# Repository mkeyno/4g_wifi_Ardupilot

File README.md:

# ArduPilot Project
This project intends to port [ArduPilot](https://github.com/ArduPilot/ardupilot) firmware on new hardware base on embedded Linux multiple-core system and ESP32.
The main purpose of this project is to extend Modular design & hardware abstract layer base on processing and task.
- ESP32 is double core processor with mature RTOS firmware. One core dedicated for IMU data fusing and main autopilot function (Stabilize, Attitude control, Navigation) other core responsible for communication, auxiliary module management and ground station. its 2.4 Ghz wifi link is sitable for local data link between drone and ground station 
- separate IO module, manage pilot commands and drone actuators data for main core system and it only exchange data on bus line in standard communication protocol (I2C, SPI, Serial), this reduce processor resources and complexity of main code, because each part is responsible for processing its own data (hardware encapsulation).IO module can be made with any designed hardware and software base on drone specification and just need to put data on TX buffer and received command from RX buffer. In this project I use same IC in Ardupilot hardware (STM32f103C8T6). Primary hardware design located at [here](Hardware/IO_Modules/readme.md) 
- Multiple-core embedded Linux system is auxiliary  core system  which can provide secondary & backup IMU data, GPS data, advance terrain navigation , 4G video streaming and any hardware management for enhancing drone capabilities. Similar to IO module this also has its own development platform base on popular Linux  
following is the block diagram and functional modules chart for this project

## Project Motivation ##
This idea came to mind when I intent to add camera on Ardupilot hardware and establish the video link under 4G network. 
SimCom 7100 & 7600 were first choice as I was familiar with Arduino GPRS shield made of SimCom product and are cheap , 
however after digging around those product I’ve noticed  the only available firmware (AT Command) is not mature enough to add camera and work as slave supplementary hardware for Ardupilot master board .
Unfortunately [SimCom]() has not provided yet any open SDK for IoT developer , hence I look to the other 4G modules in market such as [Telit]( https://www.telit.com)  , [InnoCom]( https://www.innocomm.com), [Gemalto]( https://www.gemalto.com), [Multitech]( https://www.multitech.com/), [Sierra Wireless]( https://www.sierrawireless.com), [Quectel]( https://www.quectel.com)
I found [Airprime WPx5xx-76xx series](https://source.sierrawireless.com/devices/wp-series/wp7502/) very Promising and elegant. 
while Airprime series has powerful and rich hardware with multi core, it also  embedded with Linux and open source SDK  for IoT developer 
summary of this product specification  come as follow
The AirPrime WP75xx/AirPrime WP8548 is a powerful multiple-core system that includes:
- One QDSP6 core, embedding Telecom firmware with integrated cellular voice (future firmware release), data and wireless Internet connectivity
- One Cortex-A5 core entirely dedicated to customer application and natively provided with Linux operating system
The application processor memory is dedicated to the Legato platform, including:
    - Linux kernel
    - Root file system
    - Application framework
    - Customer applications

- Memory Details WP75xx / WP8548
Flash Total 512 MB
    -256 MB Reserved for Application processor 
- RAM Total 256 MB
    -128 MB Reserved for Application processor 

## Milestone ##
- Hardware Design:
  - ***4G board***: base on Airprime
  - ***ESP32 board***:   
  - ***Input board***:   
  - ***Output board***:   
- Hardware prototype:  
- Firmware porting: 
- Test & debug: 

## License ##

This project is licensed under the GNU General Public License, version 3.

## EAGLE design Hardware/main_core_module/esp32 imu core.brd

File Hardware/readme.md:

This is repository for all hardware design and resources

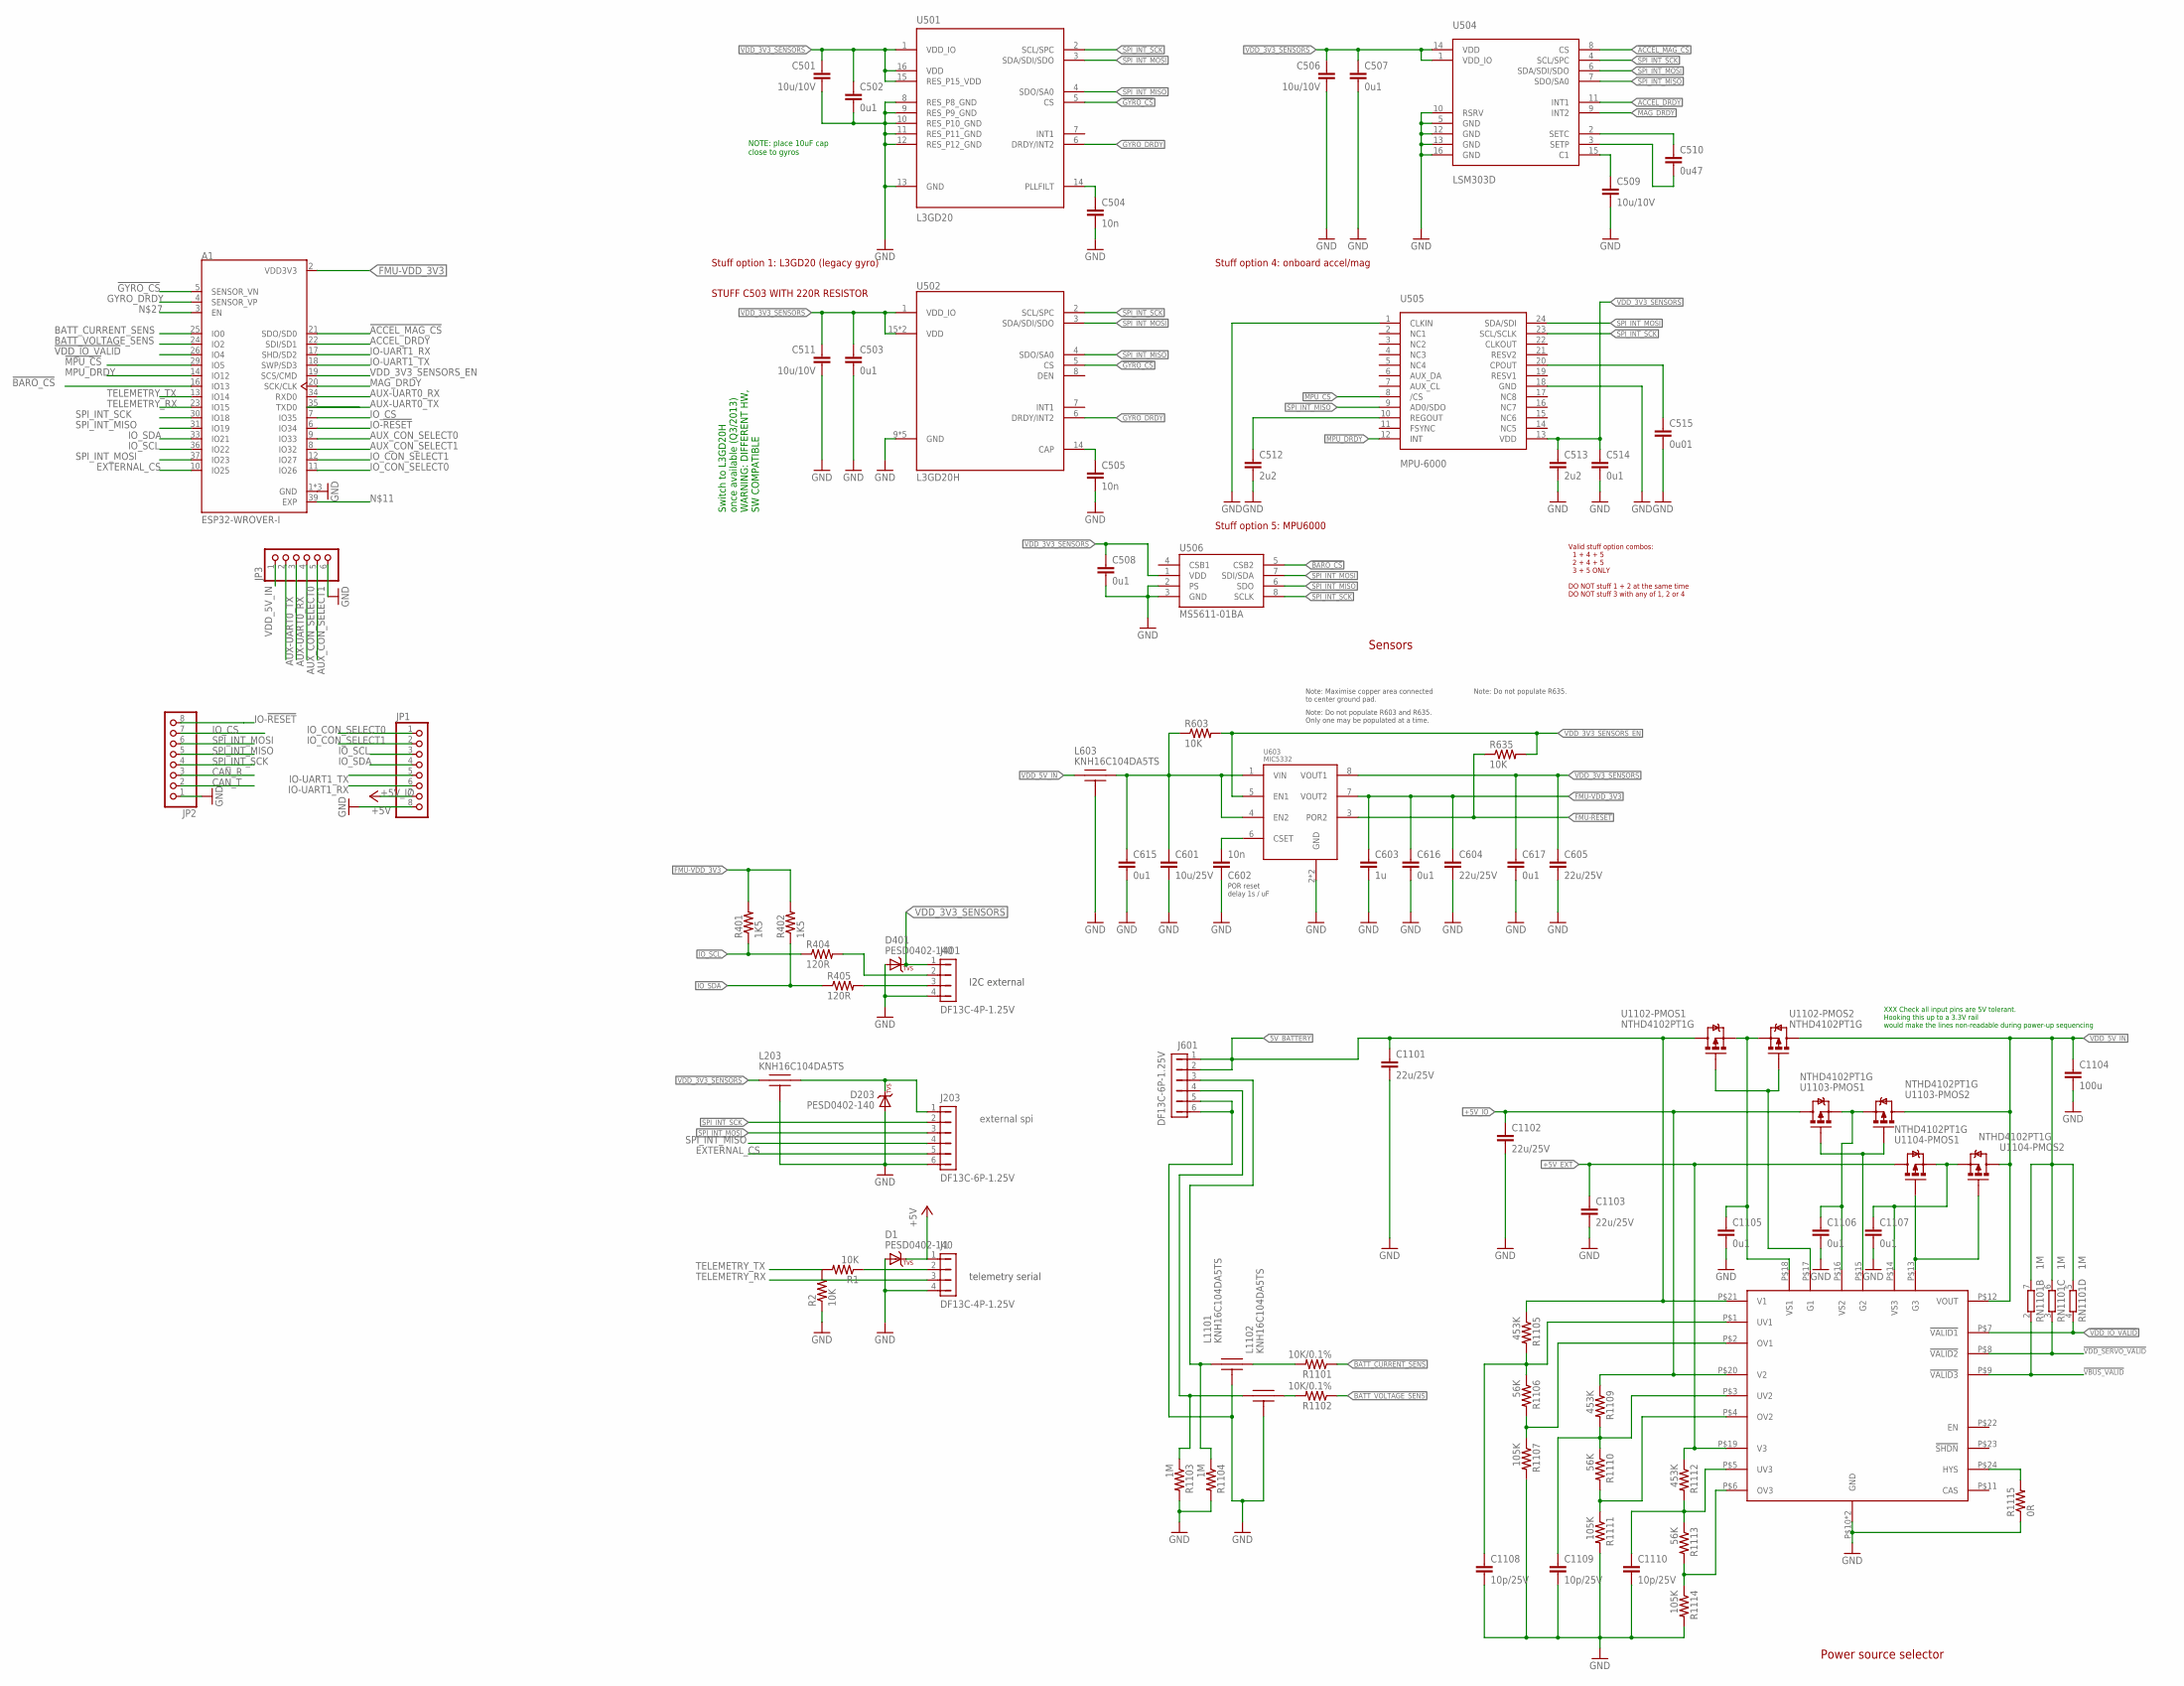
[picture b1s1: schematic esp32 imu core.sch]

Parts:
A1: ESP32-WROVER-I; XCVR_ESP32-WROVER-I
C501, C506, C509, C511: 10u/10V; 0805-CAP; PARTNO CC0805ZKY5V6BB106
C502, C503, C507, C508, C514, C615, C616, C617: 0u1; 0402-CAP; PARTNO CC0402ZRY5V7BB104
C504, C505, C602: 10n; 0402-CAP; PARTNO CC0402KRX7R7BB103
C510: 0u47; 0402-CAP; PARTNO C1005X5R1C474K050BC
C512, C513: 2u2; 0603-CAP; PARTNO C1608X6S1C225K080AC
C515: 0u01; 0603-CAP; PARTNO 06033C103JAT2A
C601: 10u/25V; 0805-CAP; PARTNO CL21A106KAYNNNE
C603: 1u; 0603-CAP; PARTNO CC0603ZRY5V7BB105
C604, C605, C1101, C1102, C1103: 22u/25V; 0805-CAP; PARTNO CL21A226MAQNNNE
C1104: 100u; 1206-CAP; PARTNO C3216X5R1A107M160AC
C1105, C1106, C1107: 0u1; 0402-CAP; PARTNO C1005X7R1E104K050BB
C1108, C1109, C1110: 10p/25V; 0402-CAP; PARTNO C0402C100J3GACTU
D1, D203, D401: PESD0402-140; 0402-TVS; PARTNO PESD0402-140
J1, J401: DF13C-4P-1.25V; PARTNO DF13C-4P-1.25V(20)
J203, J601: DF13C-6P-1.25V; PARTNO DF13C-6P-1.25V(20)
JP1, JP2: PINHD-1X8; 1X08
JP3: PINHD-1X6; 1X06
L203, L603, L1101, L1102: KNH16C104DA5TS; KYOCERA-KNH16-DA; PARTNO KNH16C104DA5TS
R1, R2, R603, R635: 10K; 0402-RES; PARTNO RC0402FR-0710KL
R401, R402: 1K5; 0402-RES; PARTNO RC0402FR-071K5L
R404, R405: 120R; 0402-RES; PARTNO RC0402FR-07120RL
R1101, R1102: 10K/0.1%; 0402-RES; PARTNO ERA-2AEB103X
R1103, R1104: 1M; 0402-RES; PARTNO RC0402FR-071ML
R1105, R1109, R1112: 453K; 0402-RES; PARTNO RMCF0402FT453K
R1106, R1110, R1113: 56K; 0402-RES; PARTNO ERA-2AEB563X
R1107, R1111, R1114: 105K; 0402-RES; PARTNO ERJ-2RKF1053X
R1115: 0R; 0402-RES; PARTNO ERJ-2GE0R00X
RN1101: 1M; EXB28V; PARTNO EXB-28V105JX
U501: L3GD20; L3G4200DH-MAN; PARTNO L3GD20
U502: L3GD20H; LGA-16L; PARTNO L3GD20H
U504: LSM303D; LGA-16L; PARTNO LSM303D
U505: MPU-6000; QFN-24; PARTNO MPU-6000
U506: MS5611-01BA; PARTNO MS5611-01BA
U603: MIC5332; MLF-8-EPAD; PARTNO MIC5332-SSYMT
U1101: LTC4417; MO-220; PARTNO LTC4417IUF#PBF
U1102, U1103, U1104: NTHD4102PT1G; 1206-8; PARTNO NTHD4102PT1G

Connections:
5V_BATTERY: C1101.P$1 (1), J601.1, J601.2, R1105.P$1 (1), U1101.P$21 (V1), U1102.P$7 (D), U1102.P$8 (D)
!ACCEL_MAG_CS: A1.21 (SDO/SD0), U504.8 (CS)
!BARO_CS: A1.16 (IO13), U506.5 (CSB2)
!GYRO_CS: A1.5 (SENSOR_VN), U501.5 (CS), U502.5 (CS)
!MPU_CS: A1.29 (IO5), U505.8 (/CS)
!VBUS_VALID: RN1101.2 (1), U1101.P$9 (!VALID3)
!VDD_IO_VALID: A1.26 (IO4), RN1101.4 (1), U1101.P$7 (!VALID1)
!VDD_SERVO_VALID: RN1101.3 (1), U1101.P$8 (!VALID2)
+5V_EXT: C1103.P$1 (1), D1.C, J1.1, R1112.P$1 (1), U1101.P$19 (V3), U1104.P$7 (D), U1104.P$8 (D)
+5V_IO: C1102.P$1 (1), JP1.7, R1109.P$1 (1), U1101.P$20 (V2), U1103.P$7 (D), U1103.P$8 (D)
ACCEL_DRDY: A1.22 (SDI/SD1), U504.11 (INT1)
AUX-UART0_RX: A1.34 (RXD0), JP3.3
AUX-UART0_TX: A1.35 (TXD0), JP3.2
AUX_CON_SELECT0: A1.9 (IO33), JP3.4
AUX_CON_SELECT1: A1.8 (IO32), JP3.5
BATT_CURRENT_SENS: A1.25 (IO0), R1101.P$1 (1)
BATT_CURRENT_SENS_PROT: J601.3, L1101.P$1, R1104.P$1 (1)
BATT_VOLTAGE_SENS: A1.24 (IO2), R1102.P$1 (1)
BATT_VOLTAGE_SENS_PROT: J601.4, L1102.P$1, R1103.P$1 (1)
CAN_R: JP2.3
CAN_T: JP2.2
EXTERNAL_CS: A1.10 (IO25), J203.5
FMU-!RESET: R635.P$1 (1), U603.3 (POR2)
FMU-VDD_3V3: A1.2 (VDD3V3), C603.P$1 (1), C604.P$1 (1), C616.P$1 (1), R401.P$2 (2), R402.P$2 (2), U603.7 (VOUT2)
FMU-VDD_5V5: C601.P$1 (1), C615.P$1 (1), L603.P$2, R603.P$1 (1), U603.1 (VIN), U603.4 (EN2)
GND: A1.1 (GND), A1.15 (GND), A1.38 (GND), C501.P$2 (2), C502.P$2 (2), C503.P$2 (2), C504.P$2 (2), C505.P$2 (2), C506.P$2 (2), C507.P$2 (2), C508.P$2 (2), C509.P$2 (2), C511.P$2 (2), C512.P$2 (2), C513.P$2 (2), C514.P$2 (2), C515.P$2 (2), C601.P$2 (2), C602.P$1 (1), C603.P$2 (2), C604.P$2 (2), C605.P$2 (2), C615.P$2 (2), C616.P$2 (2), C617.P$2 (2), C1101.P$2 (2), C1102.P$2 (2), C1103.P$2 (2), C1104.P$2 (2), C1105.P$2 (2), C1106.P$2 (2), C1107.P$2 (2), C1108.P$2 (2), C1109.P$2 (2), C1110.P$2 (2), D1.A, D203.A, D401.A, J1.4, J203.6, J401.4, J601.5, J601.6, JP1.8, JP2.1, JP3.6, L203.P$3, L203.P$4, L203.P$5, L603.P$3, L603.P$4, L603.P$5, L1101.P$3, L1101.P$4, L1101.P$5, L1102.P$3, L1102.P$4, L1102.P$5, R2.P$1 (1), R1103.P$2 (2), R1104.P$2 (2), R1107.P$2 (2), R1111.P$2 (2), R1114.P$2 (2), R1115.P$1 (1), U501.8 (RES_P8_GND), U501.9 (RES_P9_GND), U501.10 (RES_P10_GND), U501.11 (RES_P11_GND), U501.12 (RES_P12_GND), U501.13 (GND), U502.9 (GND), U502.10 (GND), U502.11 (GND), U502.12 (GND), U502.13 (GND), U504.5 (GND), U504.10 (RSRV), U504.12 (GND), U504.13 (GND), U504.16 (GND), U505.1 (CLKIN), U505.18 (GND), U506.2 (PS), U506.3 (GND), U603.2 (GND), U603.GND, U1101.P$10 (GND), U1101.P$25 (GND)
GYRO_DRDY: A1.4 (SENSOR_VP), U501.6 (DRDY/INT2), U502.6 (DRDY/INT2)
IO-!RESET: A1.6 (IO34), JP2.8
IO-UART1_RX: A1.17 (SHD/SD2), JP1.6
IO-UART1_TX: A1.18 (SWP/SD3), JP1.5
IO_CON_SELECT0: A1.11 (IO26), JP1.1
IO_CON_SELECT1: A1.12 (IO27), JP1.2
IO_CS: A1.7 (IO35), JP2.7
IO_SCL: A1.36 (IO22), JP1.3, R401.P$1 (1), R404.P$1 (1)
IO_SDA: A1.33 (IO21), JP1.4, R402.P$1 (1), R405.P$1 (1)
MAG_DRDY: A1.20 (SCK/CLK), U504.9 (INT2)
MPU_DRDY: A1.14 (IO12), U505.12 (INT)
unnamed: J1.2, R1.P$1 (1)
unnamed: C509.P$1 (1), U504.15 (C1)
unnamed: C510.P$1 (1), U504.2 (SETC)
unnamed: C510.P$2 (2), U504.3 (SETP)
unnamed: C505.P$1 (1), U502.14 (CAP)
unnamed: J401.2, R404.P$2 (2)
unnamed: C504.P$1 (1), U501.14 (PLLFILT)
unnamed: J401.3, R405.P$2 (2)
unnamed: C602.P$2 (2), U603.6 (CSET)
unnamed: C1108.P$1 (1), R1105.P$2 (2), R1106.P$1 (1), U1101.P$1 (UV1)
unnamed: C512.P$1 (1), U505.10 (REGOUT)
unnamed: C515.P$1 (1), U505.20 (CPOUT)
unnamed: R1106.P$2 (2), R1107.P$1 (1), U1101.P$2 (OV1)
unnamed: C1109.P$1 (1), R1109.P$2 (2), R1110.P$1 (1), U1101.P$3 (UV2)
unnamed: R1110.P$2 (2), R1111.P$1 (1), U1101.P$4 (OV2)
unnamed: R1113.P$2 (2), R1114.P$1 (1), U1101.P$6 (OV3)
unnamed: C1110.P$1 (1), R1112.P$2 (2), R1113.P$1 (1), U1101.P$5 (UV3)
unnamed: C1105.P$1 (1), U1101.P$18 (VS1), U1102.P$1 (S), U1102.P$3 (S)
unnamed: D203.C, J203.1, L203.P$2
unnamed: L1102.P$2, R1102.P$2 (2)
unnamed: L1101.P$2, R1101.P$2 (2)
unnamed: R1115.P$2 (2), U1101.P$24 (HYS)
unnamed: C1106.P$1 (1), U1101.P$16 (VS2), U1103.P$1 (S), U1103.P$3 (S)
unnamed: C1107.P$1 (1), U1101.P$14 (VS3), U1104.P$1 (S), U1104.P$3 (S)
unnamed: U1101.P$13 (G3), U1104.P$2 (G), U1104.P$4 (G)
unnamed: U1101.P$15 (G2), U1103.P$2 (G), U1103.P$4 (G)
unnamed: U1101.P$17 (G1), U1102.P$2 (G), U1102.P$4 (G)
SPI_INT_MISO: A1.31 (IO19), J203.4, JP2.5, U501.4 (SDO/SA0), U502.4 (SDO/SA0), U504.7 (SDO/SA0), U505.9 (AD0/SDO), U506.6 (SDO)
SPI_INT_MOSI: A1.37 (IO23), J203.3, JP2.6, U501.3 (SDA/SDI/SDO), U502.3 (SDA/SDI/SDO), U504.6 (SDA/SDI/SDO), U505.24 (SDA/SDI), U506.7 (SDI/SDA)
SPI_INT_SCK: A1.30 (IO18), J203.2, JP2.4, U501.2 (SCL/SPC), U502.2 (SCL/SPC), U504.4 (SCL/SPC), U505.23 (SCL/SCLK), U506.8 (SCLK)
TELEMETRY_RX: A1.23 (IO15), J1.3
TELEMETRY_TX: A1.13 (IO14), R1.P$2 (2), R2.P$2 (2)
VDD_3V3_SENSORS: C501.P$1 (1), C502.P$1 (1), C503.P$1 (1), C506.P$1 (1), C507.P$1 (1), C508.P$1 (1), C511.P$1 (1), C513.P$1 (1), C514.P$1 (1), C605.P$1 (1), C617.P$1 (1), D401.C, J401.1, L203.P$1, U501.1 (VDD_IO), U501.15 (RES_P15_VDD), U501.16 (VDD), U502.1 (VDD_IO), U502.15 (VDD), U502.16 (VDD), U504.1 (VDD_IO), U504.14 (VDD), U505.13 (VDD), U506.1 (VDD), U603.8 (VOUT1)
VDD_3V3_SENSORS_EN: A1.19 (SCS/CMD), R603.P$2 (2), R635.P$2 (2), U603.5 (EN1)
VDD_5V_IN: C1104.P$1 (1), JP3.1, L603.P$1, RN1101.5 (2), RN1101.6 (2), RN1101.7 (2), U1101.P$12 (VOUT), U1102.P$5 (D), U1102.P$6 (D), U1103.P$5 (D), U1103.P$6 (D), U1104.P$5 (D), U1104.P$6 (D)

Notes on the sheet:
Sensors
Switch to L3GD20H once available (Q3/2013) WARNING: DIFFERENT HW, SW COMPATIBLE
NOTE: place 10uF cap close to gyros
Stuff option 1: L3GD20 (legacy gyro)
Stuff option 4: onboard accel/mag
Valid stuff option combos: 1 + 4 + 5 2 + 4 + 5 3 + 5 ONLY DO NOT stuff 1 + 2 at the same time DO NOT stuff 3 with any of 1, 2 or 4
Stuff option 5: MPU6000
STUFF C503 WITH 220R RESISTOR
Note: Maximise copper area connected to center ground pad.
POR reset delay 1s / uF
Note: Do not populate R603 and R635. Only one may be populated at a time.
Note: Do not populate R635.
I2C external
external spi
telemetry serial
Power source selector
XXX Check all input pins are 5V tolerant. Hooking this up to a 3.3V rail would make the lines non-readable during power-up sequencing

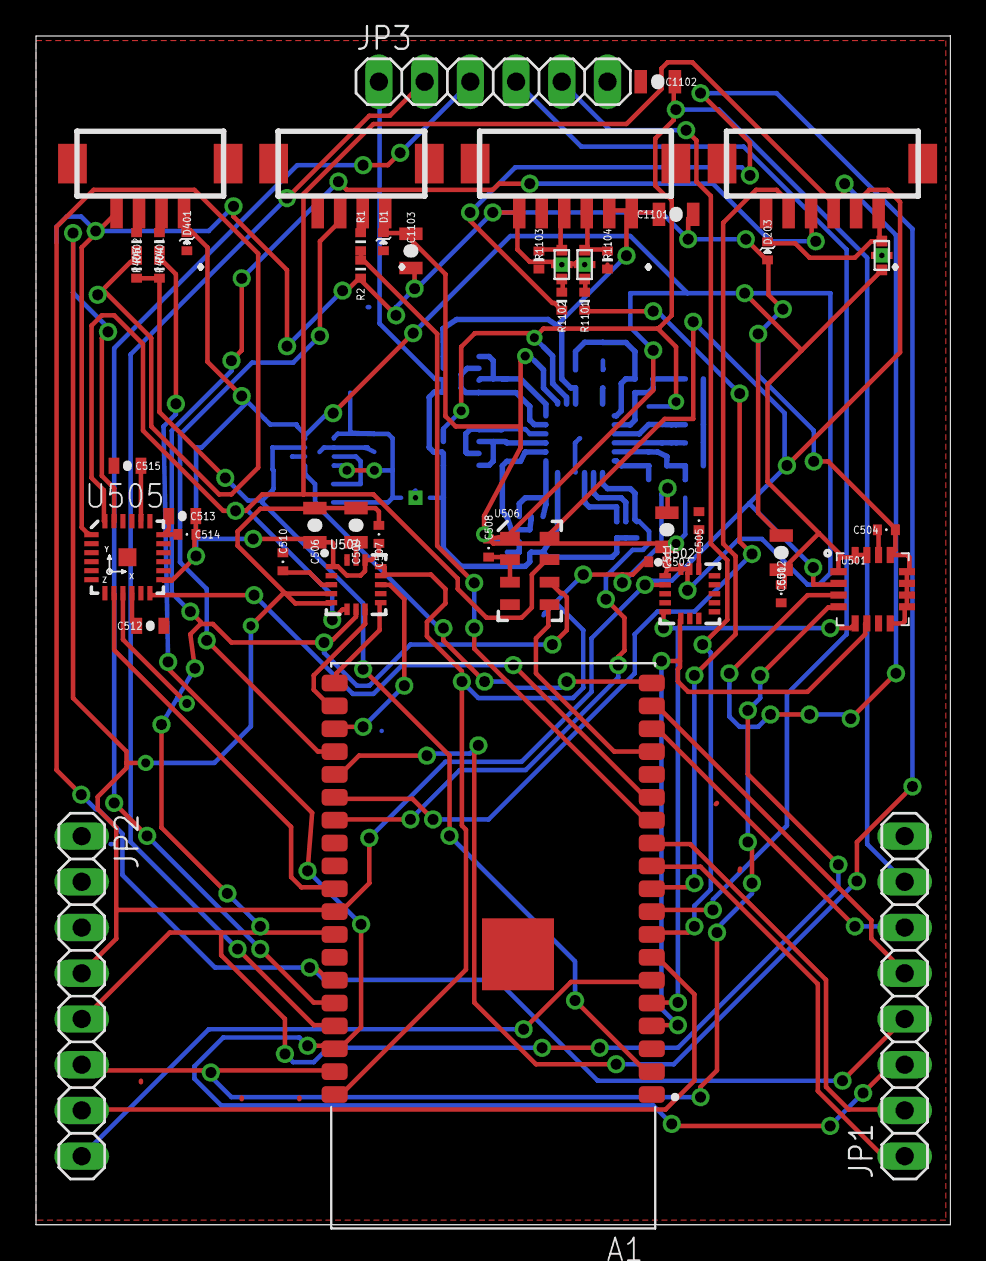
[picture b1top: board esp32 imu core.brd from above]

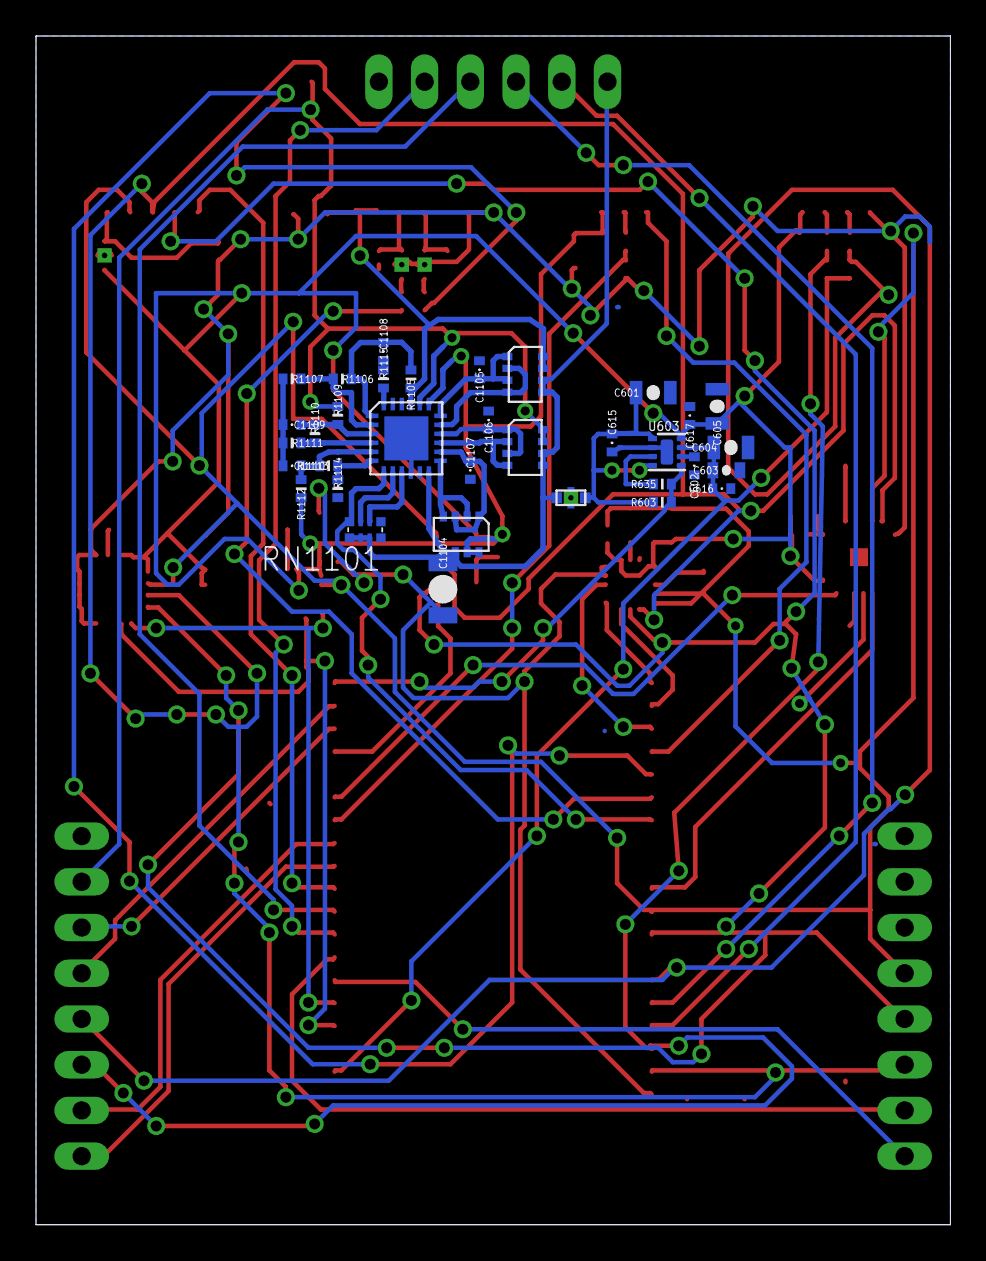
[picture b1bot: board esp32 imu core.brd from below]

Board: 2 copper layers, 50.8 x 66.0 mm, 81 parts (34 on the bottom side), 70 nets.

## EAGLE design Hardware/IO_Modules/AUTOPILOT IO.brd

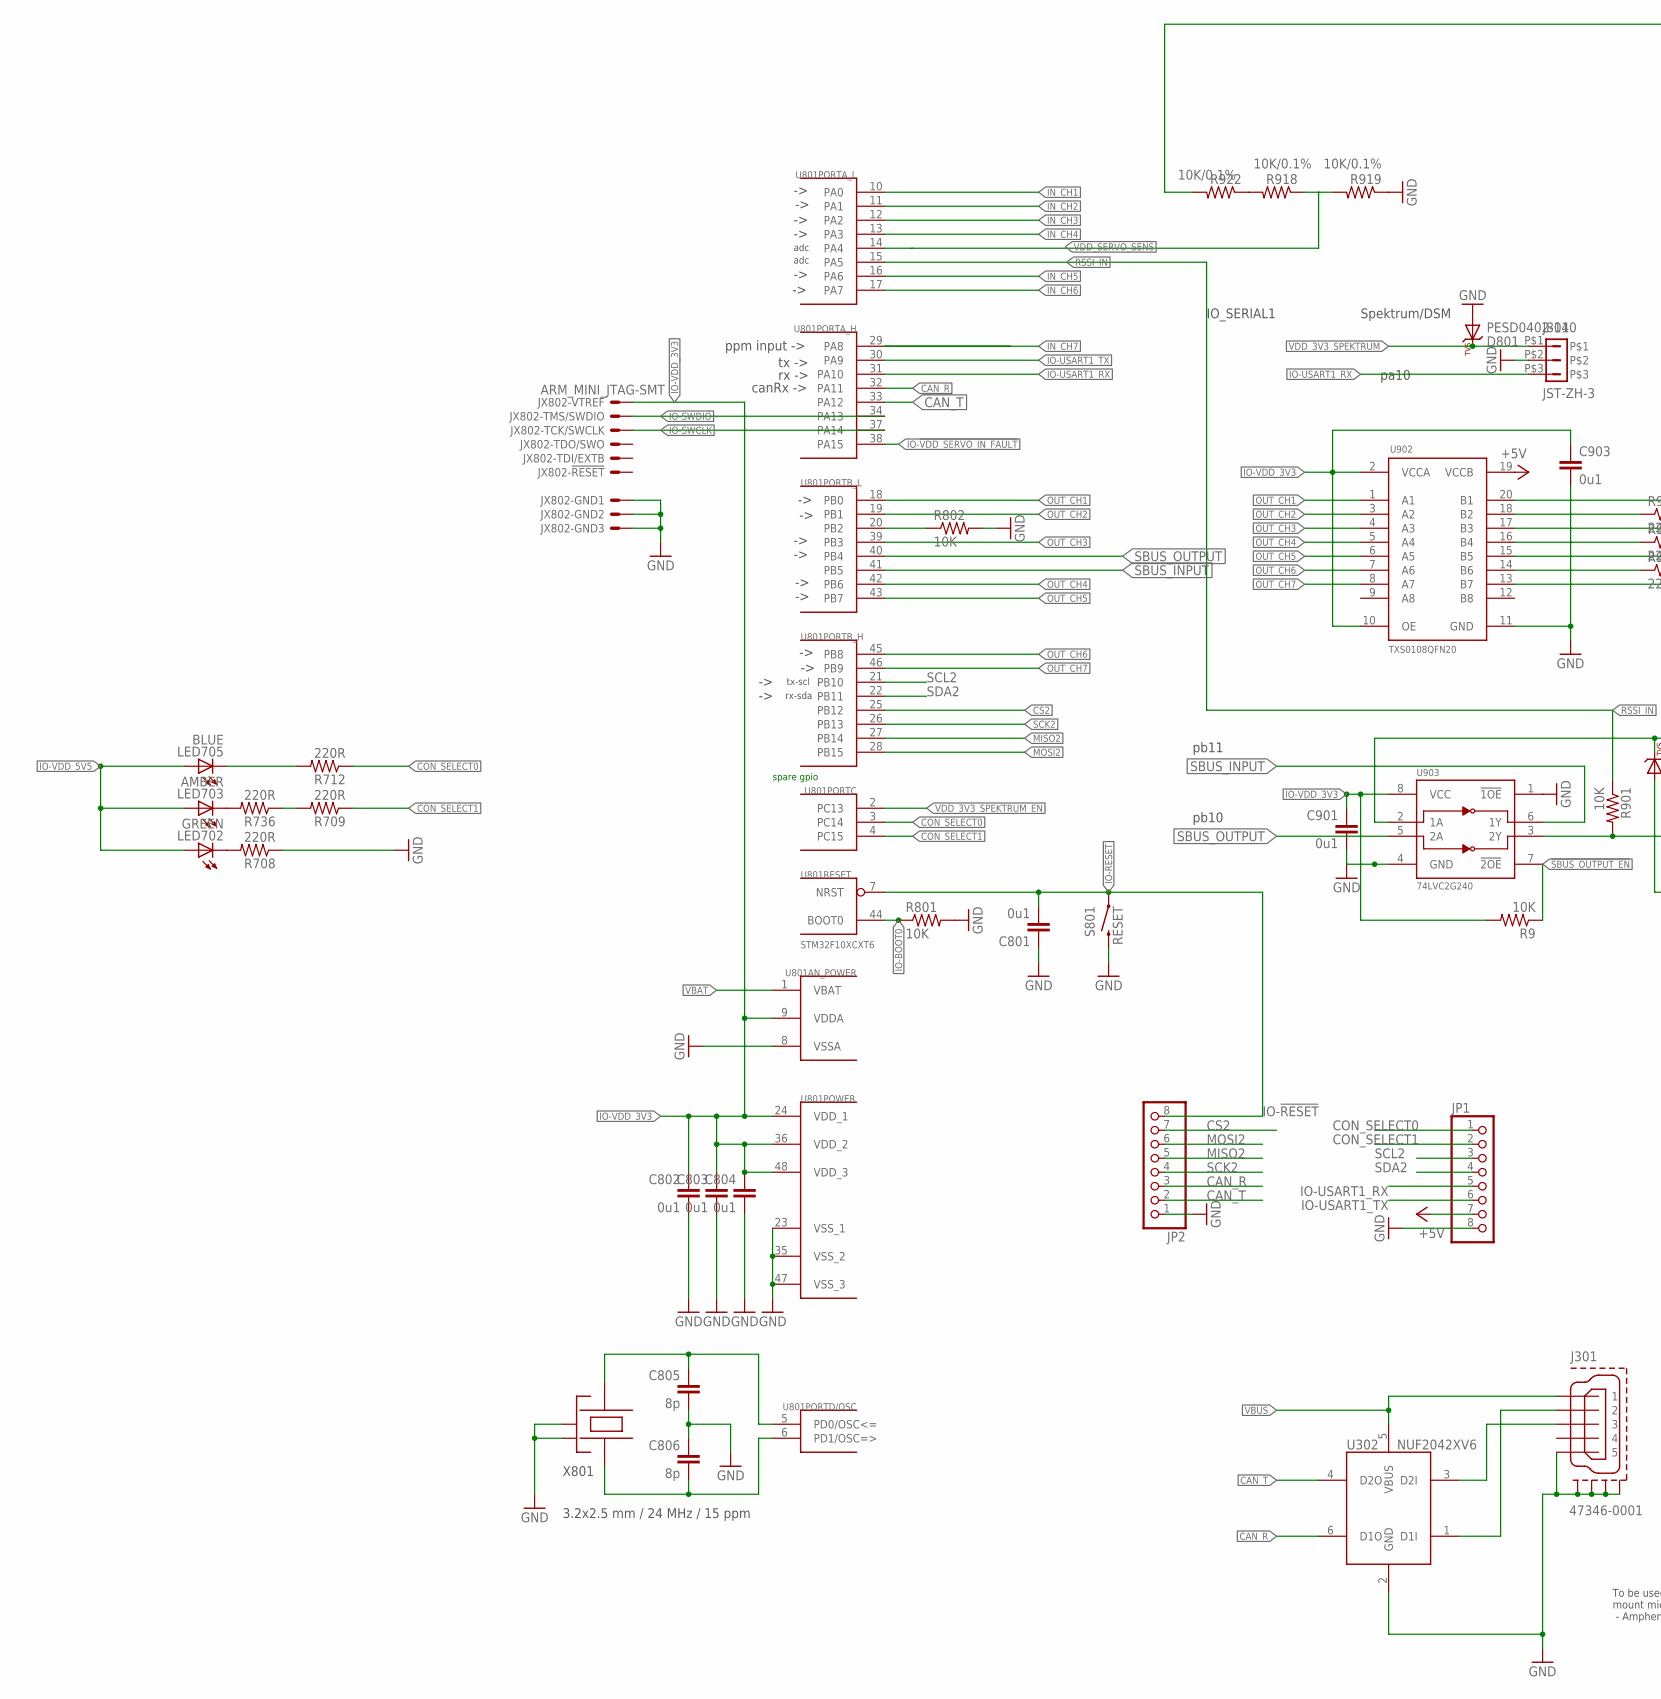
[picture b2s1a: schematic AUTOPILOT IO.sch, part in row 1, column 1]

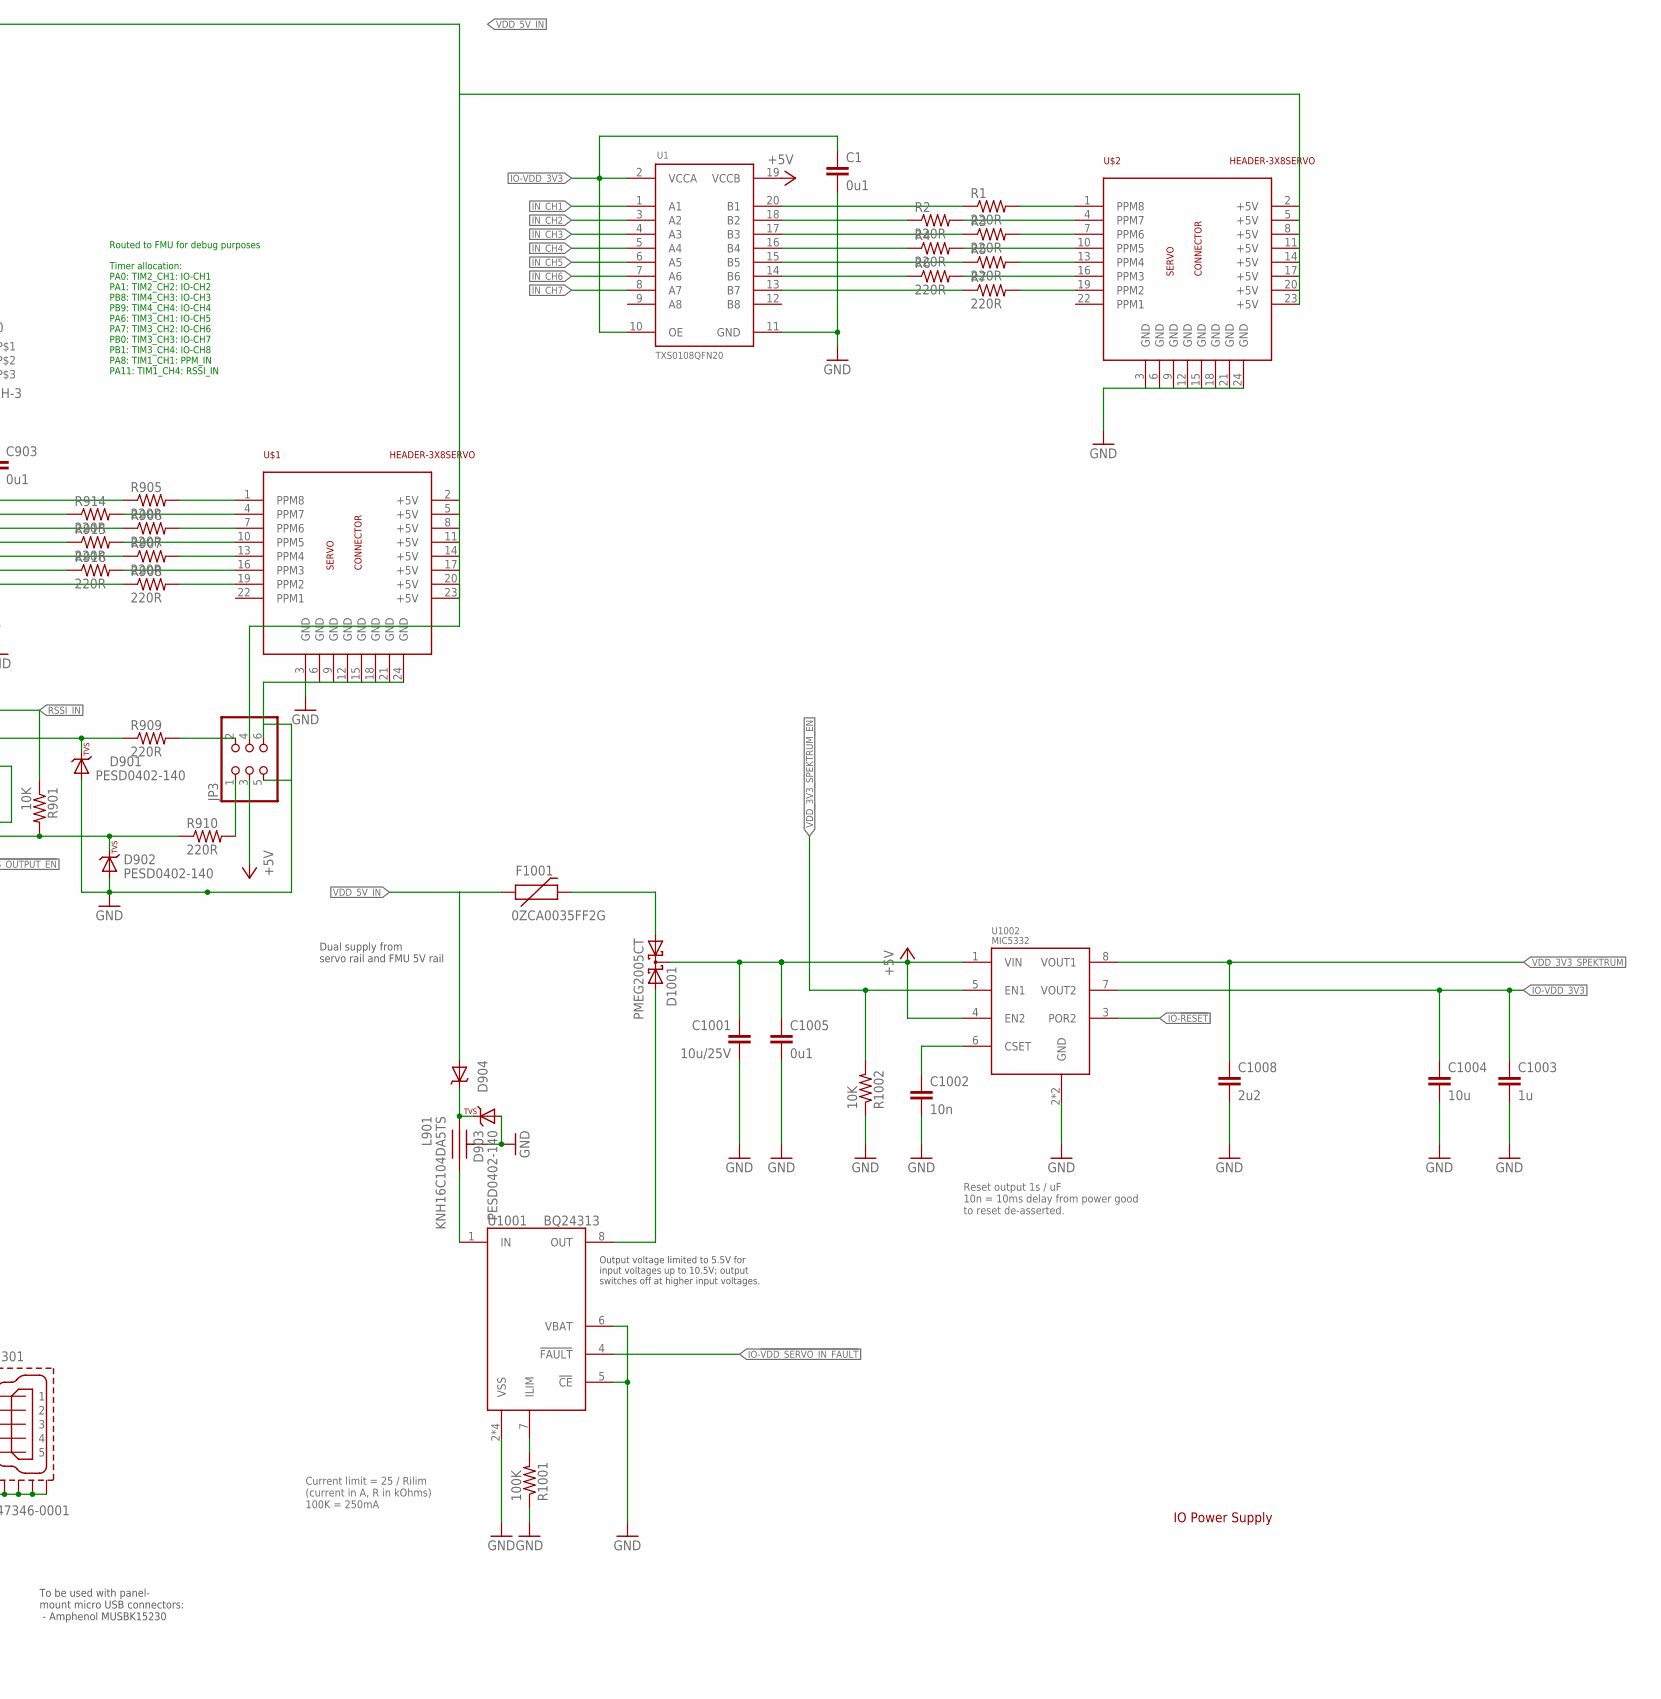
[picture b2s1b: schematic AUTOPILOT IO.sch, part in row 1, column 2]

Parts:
C1, C801, C802, C803, C804, C901, C903, C1005: 0u1; 0402-CAP; PARTNO CC0402ZRY5V7BB104
C805, C806: 8p; 0402-CAP; PARTNO C1005C0G1H080C
C1001: 10u/25V; 0805-CAP; PARTNO CL21A106KAYNNNE
C1002: 10n; 0402-CAP; PARTNO CC0402KRX7R7BB103
C1003: 1u; 0603-CAP; PARTNO CC0603ZRY5V7BB105
C1004: 10u; 0603-CAP; PARTNO C1608X5R1A106K080AC
C1008: 2u2; 0402-CAP; PARTNO C1005X6S1C225K050BC
D801, D901, D902, D903: PESD0402-140; 0402-TVS; PARTNO PESD0402-140
D904: MSS1P4-M3; MICROSMP; PARTNO MSS1P4-M3/89A
D1001: PMEG2005CT; SOT23-3; PARTNO PMEG2005CT
F1001: 0ZCA0035FF2G; PTC-1206; PARTNO 0ZCA0035FF2G
J301: 47346-0001; MOLEX-47346-0001; PARTNO 47346-0001
J801: JST-ZH-3; JST-ZH-SMT-VERTICAL; PARTNO B3B-ZR-SM4-TF (LF)(SN)(P)
JP1, JP2: PINHD-1X8; 1X08
JP3: PINHD-2X3; 2X03
JX802: ARM_MINI_JTAG-SMT; FTSH-105-01-XXX-DV-K; PARTNO M50-3900542
L901: KNH16C104DA5TS; KYOCERA-KNH16-DA; PARTNO KNH16C104DA5TS
LED702: GREEN; 0603-LED; PARTNO APTD1608CGCK
LED703: AMBER; 0603-LED; PARTNO APTD1608SECK
LED705: BLUE; 0603-LED; PARTNO APTD1608QBC/D
R1, R2, R3, R4, R5, R6, R7, R708, R709, R712, R736, R905, R906, R907, R908, R909, R910, R914, R915, R916: 220R; 0402-RES; PARTNO RC0402FR-07220RL
R9, R801, R802, R901, R1002: 10K; 0402-RES; PARTNO RC0402FR-0710KL
R918, R919, R922: 10K/0.1%; 0402-RES; PARTNO ERA-2AEB103X
R1001: 100K; 0402-RES; PARTNO RC0402FR-07100KL
S801: RESET; EVQP7J01K; PARTNO EVQ-P7J01P
U1, U902: TXS0108QFN20; QFN20-RGY; PARTNO TXS0108ERGYR
U302: NUF2042XV6; SOT563-6; PARTNO NUF2042XV6T1G
U801: STM32F10XCXT6; TQFP48; PARTNO STM32F100C8T6B
U903: 74LVC2G240; TSSOP8_SOT505-2; PARTNO 74LVC2G240DP,125
U1001: BQ24313; QFN8-DSG; PARTNO BQ24313DSGT
U1002: MIC5332; MLF-8-EPAD; PARTNO MIC5332-SSYMT
U$1, U$2: HEADER-3X8SERVO; 3X8RA
X801: 3.2x2.5 mm / 24 MHz / 15 ppm; OSCILLATOR-3.2X2.5; PARTNO NX3225SA-24.000000MHZ

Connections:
!SBUS_OUTPUT_EN: R9.P$1 (1), U903.7 (!2OE)
+5V: C1001.P$1 (1), C1005.P$1 (1), D1001.3 (CC), JP1.7, JP3.3, U1.19 (VCCB), U902.19 (VCCB), U1002.1 (VIN), U1002.4 (EN2)
CAN_R: JP2.3, U302.6 (D1O), U801.32 (PA11)
CAN_T: JP2.2, U302.4 (D2O), U801.33 (PA12)
CON_SELECT0: JP1.1, R712.P$1 (1), U801.3 (PC14)
CON_SELECT1: JP1.2, R709.P$1 (1), U801.4 (PC15)
CS2: JP2.7, U801.25 (PB12)
GND: C1.P$2 (2), C801.P$1 (1), C802.P$2 (2), C803.P$2 (2), C804.P$2 (2), C805.P$2 (2), C806.P$1 (1), C901.P$2 (2), C903.P$2 (2), C1001.P$2 (2), C1002.P$2 (2), C1003.P$2 (2), C1004.P$2 (2), C1005.P$2 (2), C1008.P$2 (2), D801.A, D901.A, D902.A, D903.A, J301.GND (5), J301.GND1, J301.GND2, J301.GND3, J301.GND4, J801.P$2, JP1.8, JP2.1, JP3.5, JP3.6, JX802.3, JX802.5, JX802.9, L901.P$3, L901.P$4, L901.P$5, R708.P$1 (1), R801.P$2 (2), R802.P$2 (2), R919.P$1 (1), R1001.P$1 (1), R1002.P$1 (1), S801.B3 (2), U1.11 (GND), U302.2 (GND), U801.8 (VSSA), U801.23 (VSS_1), U801.35 (VSS_2), U801.47 (VSS_3), U902.11 (GND), U903.1 (!1OE), U903.4 (GND), U1001.2 (VSS), U1001.5 (!CE), U1001.6 (VBAT), U1001.GND (VSS), U1001.P$2 (VSS), U1001.P$3 (VSS), U1002.2 (GND), U1002.GND, U$1.3 (GND), U$1.6 (GND), U$1.9 (GND), U$1.12 (GND), U$1.15 (GND), U$1.18 (GND), U$1.21 (GND), U$1.24 (GND), U$2.3 (GND), U$2.6 (GND), U$2.9 (GND), U$2.12 (GND), U$2.15 (GND), U$2.18 (GND), U$2.21 (GND), U$2.24 (GND), X801.2 (NC_2), X801.4 (NC_4)
IN_CH1: U1.1 (A1), U801.10 (PA0)
IN_CH2: U1.3 (A2), U801.11 (PA1)
IN_CH3: U1.4 (A3), U801.12 (PA2)
IN_CH4: U1.5 (A4), U801.13 (PA3)
IN_CH5: U1.6 (A5), U801.16 (PA6)
IN_CH6: U1.7 (A6), U801.17 (PA7)
IN_CH7: D901.C, R909.P$1 (1), U1.8 (A7), U801.29 (PA8), U903.2 (1A)
IO-!RESET: C801.P$2 (2), JP2.8, S801.A1 (1), U801.7 (NRST), U1002.3 (POR2)
IO-!VDD_SERVO_IN_FAULT: U801.38 (PA15), U1001.4 (!FAULT)
IO-BOOT0: R801.P$1 (1), U801.44 (BOOT0)
IO-BOOT1: R802.P$1 (1), U801.20 (PB2)
IO-CH8-PROT: R905.P$2 (2), U$1.1 (PPM8)
IO-CH8-PROT1: R1.P$2 (2), U$2.1 (PPM8)
IO-SWCLK: JX802.4, U801.37 (PA14)
IO-SWDIO: JX802.2, U801.34 (PA13)
IO-USART1_RX: J801.P$3, JP1.5, U801.31 (PA10)
IO-USART1_TX: JP1.6, U801.30 (PA9)
IO-VDD_3V3: C1.P$1 (1), C802.P$1 (1), C803.P$1 (1), C804.P$1 (1), C901.P$1 (1), C903.P$1 (1), C1003.P$1 (1), C1004.P$1 (1), JX802.1, R9.P$2 (2), U1.2 (VCCA), U1.10 (OE), U801.9 (VDDA), U801.24 (VDD_1), U801.36 (VDD_2), U801.48 (VDD_3), U902.2 (VCCA), U902.10 (OE), U903.8 (VCC), U1002.7 (VOUT2)
IO-VDD_5V5: LED702.A, LED703.A, LED705.A
MISO2: JP2.5, U801.27 (PB14)
MOSI2: JP2.6, U801.28 (PB15)
unnamed: D1001.2 (A2), U1001.8 (OUT)
unnamed: R1.P$1 (1), U1.20 (B1)
unnamed: R918.P$2 (2), R922.P$1 (1)
unnamed: R2.P$1 (1), U1.18 (B2)
unnamed: R3.P$1 (1), U1.17 (B3)
unnamed: R4.P$1 (1), U1.16 (B4)
unnamed: R5.P$1 (1), U1.15 (B5)
unnamed: R6.P$1 (1), U1.14 (B6)
unnamed: LED705.C, R712.P$2 (2)
unnamed: R7.P$1 (1), U1.13 (B7)
unnamed: R3.P$2 (2), U$2.7 (PPM6)
unnamed: R4.P$2 (2), U$2.10 (PPM5)
unnamed: R5.P$2 (2), U$2.13 (PPM4)
unnamed: R6.P$2 (2), U$2.16 (PPM3)
unnamed: R7.P$2 (2), U$2.19 (PPM2)
unnamed: R2.P$2 (2), U$2.4 (PPM7)
unnamed: C806.P$2 (2), U801.6 (PD1/OSC=>), X801.1
unnamed: L901.P$2, U1001.1 (IN)
unnamed: R1001.P$2 (2), U1001.7 (ILIM)
unnamed: C805.P$1 (1), U801.5 (PD0/OSC<=), X801.3
unnamed: LED702.C, R708.P$2 (2)
unnamed: R914.P$2 (2), U$1.4 (PPM7)
unnamed: D902.C, R901.P$2 (2), R910.P$1 (1), U903.3 (2Y)
unnamed: R709.P$2 (2), R736.P$1 (1)
unnamed: LED703.C, R736.P$2 (2)
unnamed: R905.P$1 (1), U902.20 (B1)
unnamed: R914.P$1 (1), U902.18 (B2)
unnamed: R906.P$1 (1), U902.17 (B3)
unnamed: D1001.1 (A1), F1001.2
unnamed: R915.P$1 (1), U902.16 (B4)
unnamed: R907.P$1 (1), U902.15 (B5)
unnamed: R916.P$1 (1), U902.14 (B6)
unnamed: R908.P$1 (1), U902.13 (B7)
unnamed: R906.P$2 (2), U$1.7 (PPM6)
unnamed: R915.P$2 (2), U$1.10 (PPM5)
unnamed: R907.P$2 (2), U$1.13 (PPM4)
unnamed: R916.P$2 (2), U$1.16 (PPM3)
unnamed: R908.P$2 (2), U$1.19 (PPM2)
unnamed: JP3.1, R910.P$2 (2)
unnamed: C1002.P$1 (1), U1002.6 (CSET)
unnamed: D903.C, D904.CATHODE (C), L901.P$1
OTG_DM1: J301.D- (2), U302.1 (D1I)
OTG_DP1: J301.D+ (3), U302.3 (D2I)
OUT_CH1: U801.18 (PB0), U902.1 (A1)
OUT_CH2: U801.19 (PB1), U902.3 (A2)
OUT_CH3: U801.39 (PB3), U902.4 (A3)
OUT_CH4: U801.42 (PB6), U902.5 (A4)
OUT_CH5: U801.43 (PB7), U902.6 (A5)
OUT_CH6: U801.45 (PB8), U902.7 (A6)
OUT_CH7: U801.46 (PB9), U902.8 (A7)
PPM-SBUS-PROT: JP3.2, R909.P$2 (2)
RSSI_IN: R901.P$1 (1), U801.15 (PA5)
SBUS_INPUT: U801.41 (PB5), U903.6 (1Y)
SBUS_OUTPUT: U801.40 (PB4), U903.5 (2A)
SCK2: JP2.4, U801.26 (PB13)
SCL2: JP1.3, U801.21 (PB10)
SDA2: JP1.4, U801.22 (PB11)
VBAT: U801.1 (VBAT)
VBUS: J301.VBUS (1), U302.5 (VBUS)
VDD_3V3_SPEKTRUM: C1008.P$1 (1), D801.C, J801.P$1, U1002.8 (VOUT1)
VDD_3V3_SPEKTRUM_EN: R1002.P$2 (2), U801.2 (PC13), U1002.5 (EN1)
VDD_5V_IN: D904.ANODE (A), F1001.1, JP3.4, R922.P$2 (2), U$1.2 (+5V), U$1.5 (+5V), U$1.8 (+5V), U$1.11 (+5V), U$1.14 (+5V), U$1.17 (+5V), U$1.20 (+5V), U$1.23 (+5V), U$2.2 (+5V), U$2.5 (+5V), U$2.8 (+5V), U$2.11 (+5V), U$2.14 (+5V), U$2.17 (+5V), U$2.20 (+5V), U$2.23 (+5V)
VDD_SERVO_SENS: R918.P$1 (1), R919.P$2 (2), U801.14 (PA4)

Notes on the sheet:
Routed to FMU for debug purposes
IO_SERIAL1
Spektrum/DSM
Timer allocation: PA0: TIM2_CH1: IO-CH1 PA1: TIM2_CH2: IO-CH2 PB8: TIM4_CH3: IO-CH3 PB9: TIM4_CH4: IO-CH4 PA6: TIM3_CH1: IO-CH5 PA7: TIM3_CH2: IO-CH6 PB0: TIM3_CH3: IO-CH7 PB1: TIM3_CH4: IO-CH8 PA8: TIM1_CH1: PPM_IN PA11: TIM1_CH4: RSSI_IN
spare gpio
ppm input ->
tx ->
rx ->
canRx ->
tx-scl
rx-sda
adc
pb11
pb10
Dual supply from servo rail and FMU 5V rail
Current limit = 25 / Rilim (current in A, R in kOhms) 100K = 250mA
IO Power Supply
Reset output 1s / uF 10n = 10ms delay from power good to reset de-asserted.
Output voltage limited to 5.5V for input voltages up to 10.5V; output switches off at higher input voltages.
pa10
To be used with panel- mount micro USB connectors: - Amphenol MUSBK15230

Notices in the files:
parts and their libraries:
SparkFun-Resistors: Licensing: Creative Commons ShareAlike 4.0 International - https://creativecommons.org/licenses/by-sa/4.0
